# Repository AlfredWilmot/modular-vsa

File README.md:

# Modular VSA

A 3D-printed robot utilizing variable-stiffness-actuators (VSAs), see below for more information:

<table>
  <!-- This is a HTML comment! -->
  <col width="50%">
  <col width="50%">
  <tr>
    <th><font size=5>Publication</font></th>
    <th><font size=5>Poster</font></th>
  </tr>
  <tr>
    <tr>
    <th>
      
      <a href="https://doi.org/10.1007/978-3-030-89177-0_24">
        <font size=3>https://doi.org/10.1007/978-3-030-89177-0_24</font>
      </a>
    </th>
    <th rowspan="3">
      
        <font size=3>(click image to expand)</font>
    </th>
  </tr>
  <tr>
    <th><font size=5>Presentation</font></th>
  </tr>
  <tr>
    <th>
      
      <a href="https://doi.org/10.1007/978-3-030-89177-0_24">
        <font size=3>https://youtu.be/8nxKKBM5YlE</font>
      </a>
    </th>
  </tr>
</table>

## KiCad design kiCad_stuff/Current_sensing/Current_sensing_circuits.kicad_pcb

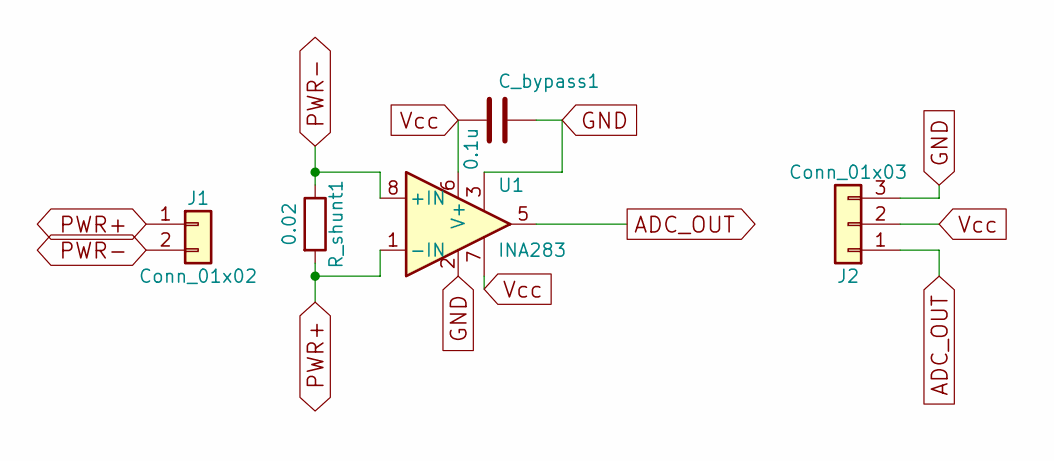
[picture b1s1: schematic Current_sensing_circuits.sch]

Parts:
C_bypass1: 0.1u; C_0805
J1: Conn_01x02; PinSocket_1x02_P2.54mm_Vertical
J2: Conn_01x03; PinSocket_1x03_P2.54mm_Vertical
R_shunt1: 0.02; R_2512
U1: INA283; SOIC-8-N

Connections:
ADC_OUT: J2.1, U1.5
GND: C_bypass1.1, J2.3, U1.2, U1.3
PWR+: J1.1, R_shunt1.2, U1.1 (-IN)
PWR-: J1.2, R_shunt1.1, U1.8 (+IN)
Vcc: C_bypass1.2, J2.2, U1.6 (V+), U1.7

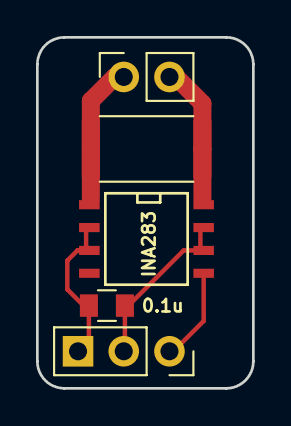
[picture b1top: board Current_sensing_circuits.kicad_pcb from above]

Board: 2 copper layers, 12.0 x 19.5 mm, 5 parts (0 on the bottom side), 5 nets.

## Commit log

2018-11-05 Arduino sketch for testing AS5600 I2C
    AS5600: 12-bit Rotary magnetic encoder with I2C interface.
2018-11-05 Added AS5600 Arduino submodule
2018-12-15 Setup kiCad proj, and added AS5600_ASOM to proj-specific lib.
2018-12-15 added mounting holes
2018-12-15 Added proj footptint symbol lib with 2 user-made footprints
2018-12-15 Parts except pins in position
2018-12-15 Added PCB perimeter
2018-12-15 Ethernet-cable direct solder v2 completed
2018-12-15 That symmetry tho
2018-12-15 fixed pin text on vEth2
2018-12-15 Added version with molex connector
2019-01-14 Picture of Eth_v2 AS5600 PCB
2019-01-14 Regenerated ground plane as was overlapping a track
2019-01-14 moved pic
2019-01-14 generated gerber files for Eth_v2 AS5600 PCB
2019-01-30 Bit-banging I2C over digital I/O pins
2019-01-30 housekeeping
2019-02-02 Simple script for running segment in open-loop mode using single L298N motor driver
2019-02-03 Fixed comment typo
2019-02-23 Started designing PCB using ADC-to-I2C chip
2019-03-01 More slave-device addresses using ADC-to-I2C converter.
2019-03-01 Tweaking encoder PCB dimensions
2019-03-01 some minor tweaks
2019-03-10 storing old changes, as a precaution.
2019-03-10 matlab
2019-03-10 DH parameters done
2019-03-10 Sample 3D heat-map plot of experienced joint-torque for all joint configs
2019-03-13 Added current-sensing PCB design, need to add labels
2019-03-13 1mm trackwidth for shunt-resistor tracks
2019-03-17 Setting up MCP2331 test code
2019-03-17 Added generic I2C scanning script for Arduino.
2019-03-17 Added MCP3221 Arduino driver from external git repo
2019-03-17 Can link to MCP3221 repo via Arduino IDE
2019-03-17 Can talk to one encoder so far
2019-03-17 Setting up ros workspace, starting with a package for joint encoders
2019-03-17 Added user-made library to cmake
2019-03-17 added third-party MCP3221 driver code
2019-03-17 Attempting to setup platformIO project with Arduino for now
2019-03-18 Direct path to MCP3221 lib from main.cpp, and had to remove Wire.h from MCP3221.h
2019-03-18 Test code works: had to manually place MCP3221 repo into lib folder, and remove non-cpp files.
2019-03-18 Publisher working with Arduino Micro, added README in HELLO_ROS
2019-03-18 Publishing data from single encoder to ROS using rosserial-arduino
2019-03-18 teaks and READMEs
2019-03-19 Added company logo to PCB library
2019-03-20 added package for testing single antagonist joint, using Arduino Micro
2019-03-20 Using xbox360 gamepad to control segment via ros
2019-03-20 Added readme with ROS gamepad setup info
2019-03-20 Made simple subscriber for reading xbox-360 gamepad
2019-03-21 Configured pins for L298N driver of proximal joint, verified in code. Can begin developing controller now!
2019-03-21 Corrected Arduino Micro pinout schematic and link.
2019-03-21 Adding more info to joystick README
2019-03-21 Experimenting with some basic gamepad control
2019-03-21 Correct Arduino Micro pinout schematic
2019-03-23 Made launch-file for automating game-pad setup and game-pad parser node
2019-03-23 basic joy-stick parser working with roslaunch
2019-03-23 Using UInt8 data-type for motor msg array
2019-03-24 successful open-loop control of single segment joint while using xbox360 controller
2019-03-24 tweaking motor controller
2019-03-24 automated arduino message forwarding at higher baud
2019-03-24 some reorganization to reduce dynamic memory whoring
2019-03-24 Publisher/ Subscriber setup works on Arduino Micro, just not when attempting to publish encoder data (only dummy-value).
2019-03-24 Simultaneous publishing of proximal joint encoder & subscribing to filtered gamepad msg
2019-03-24 Experimenting with STM32F103C8T6 serial communication
2019-03-25 Sampling of two I2C encoders on same BUS and display on rqt_plot
2019-03-25 Placing I2C scanner sketch into it's own folder for use with ARduino IDE
2019-03-25 Removing redundant MCP3221.h libreary, and cleaning up code
2019-03-26 Improved joystick parser functionality, by using filter and btn-debounce. Using xbox-button to toggle between control of either joint.
2019-03-26 Simultaneously have direct control over both joints with gamepad, and both encoders publishing their values.
2019-03-26 Adding functionality for parsing axis float values
2019-03-26 Added float to uint8_t mapping function
2019-03-26 Removed silly buffer-overflow bug, and captured axes indices
2019-03-26 Almost done with axes parsing, but default axes values are all 0, even though trigger resting position is 1.0
2019-03-26 Initial trigger resting value now shows 255 on segment_motor_cmd topic as it should
2019-03-26 Wider deadband for joy-stick resting position to mitigate false motor cmds
2019-03-26 added toggle-switch for joy-stick OL controller, and cleaned up parsing code a bit, ready to make OL controller
2019-03-28 latest curernt sensing gerber files
2019-03-28 Testing Freddy's Fusion360 Addin: URDF generator
2019-03-28 Second attempt with more well-defined joints, and single-body-links
2019-03-28 Test 2
2019-03-30 making Gazebo launch file, and added dummy mass/ inertia values to successfully get robot model to spawn
2019-03-30 Added dummy unit joint transmissions, and a arm_controller yaml in order to play with sim/ motion planning
2019-03-31 added gazebo joint_state publisher plugin
2019-03-31 using robot_state_publisher pkg to generate tf msgs by doing fwd kinematics to joint_state msgs
2019-03-31 ran MoveIt! config wizard to generate a MoveIt! pkg. Gazebo not responding to moveit msgs, debugging.
2019-04-09 Setting up parts list for embedded PCB
2019-04-09 Rename parts_list.md to README.md
2019-04-11 Added another H-bridge motor driver to consider
2019-04-11 resolved joint_controller bug (Assign effort & velocity limits > 0 to joint limits in URDF), and addressed gravity bug
2019-04-12 Reran MoveIt! setup assistant, and added controller.yaml file to moveit config folder to show controller follow_joint_trajectory action
2019-04-12 using JointTrajectoryController for effort_controllers, which is compatible with MoveIt! motion planner
2019-04-12 MoveIt! needs to be able to see joint_states to verify path-planning, ensure that it is looking in the correct namespace
2019-04-14 updating README
2019-04-14 Adding new URDF package from URDF generator
2019-04-14 Generated URDF had bad link origins, deleting asociated package
2019-04-14 Added new package for 8dof version of SARA
2019-04-15 Simulated 8-DOF segment in gazebo, PID controllers are tricky to tune; using XACRO to simplify URDF
2019-04-15 automating urdf gen by placing xacro params in launch files
2019-04-15 added damping to prevent issues with joint jittering around axis in gazebo sim
2019-04-15 basic path-planning for 8DOF SARA
2019-04-15 reduced damping factor for more efficient movements
2019-04-15 Backing up the latest segment design
2019-04-16 Wheelchair with Shoulder from URDF generator
2019-04-16 Getting display.launch
2019-04-16 saving rviz config
2019-04-16 Have a basic URDF with the wheelchair and 8DOF segment (too short)
2019-04-16 Added another segment to chain
2019-04-16 A basic URDF of the segments with a rigid link element
2019-04-16 Added stl for rigid link
2019-04-16 poorly defined URDF
2019-04-17 lined-up rigid link with shoulder
2019-04-17 lined-up rigid link with segment base
2019-04-17 xacro for rigid link connection to segment base
2019-04-17 setting up xacro for simplifying rigid-link + segment URDF
2019-04-17 Automated appending to manipulator chain using xacro
2019-04-17 finalizing URDF for gazebo
2019-04-17 gazebo sim appears to be working
2019-04-17 Motion-planner setup, just need to tweak gazebo URDF parameters
2019-04-19 exploring cable length variation equations
2019-04-19 observing roughly linear response of cable length variations
2019-04-19 saving picture of ~linear-response plot
2019-04-19 equation for motor velocity to drive joint from one position to another (consider fitting sinusoid to this-- i.e. peak acceleration when half-way to target)
2019-04-21 Added missing joints to gazebo control plugin in xacro file
2019-04-21 tested current sensing using stm-bluepill, test ROS integration
2019-04-22 got blue-pill to work with ros and a janky H-bridge to drive the segment
2019-04-30 Adding set of sanity-check functions for testing each element of a single segment mounted to the test-base. Using Arduino Micro.
2019-04-30 Pins on Arduino Micro MCU are calibrated for antagonist actuation
2019-04-30 made a new, simplified gamepad parser (sends filtered binary array to segment_motor_cmds topic)
2019-04-30 have OL control of single segment, using new base (but both joint dirs are inverted)
2019-05-02 Installed Teensy_3.2 into testbench; all sensor data can be published and I-sense doesn't exceed 3.3V
2019-05-02 Experimenting with STM32F1038C (blue-pill) serial interface: good exercise for when one processor will be embedded into each segment
2019-05-03 stuff
2019-05-09 Testing workspace visualization code from Ian
2019-05-09 Mapping workspace of segment chains
2019-05-09 Adding pictures for report
2019-05-10 fixing URDF name issue with single segment sim
2019-05-10 removing unnecessary serial lib
2019-05-12 Adjustment to code after rewiring hardware so I-sense doesn't exceed ADC tolerance (3.3V)
2019-05-12 Changing code to reflect hardware changes
2019-05-13 some minor readjustment, and tweaks to reflect hardware changes.
2019-05-13 integrated direct motor commands into OL controller (testing indicates direct-control works, can now attempt CL control)
2019-05-13 started integrating simple CL control to hold the current position; need to debug corrective term
2019-05-13 CL code appears to be integrated into OL controller, now need to tune CL controller
2019-05-15 We're back, for a demo baby!
2019-05-15 simple CL controller (no speed control atm, just dir) for proximal joint
2019-05-15 Simple CL controller operational
2019-07-12 Adding link to demo video, and poster img
